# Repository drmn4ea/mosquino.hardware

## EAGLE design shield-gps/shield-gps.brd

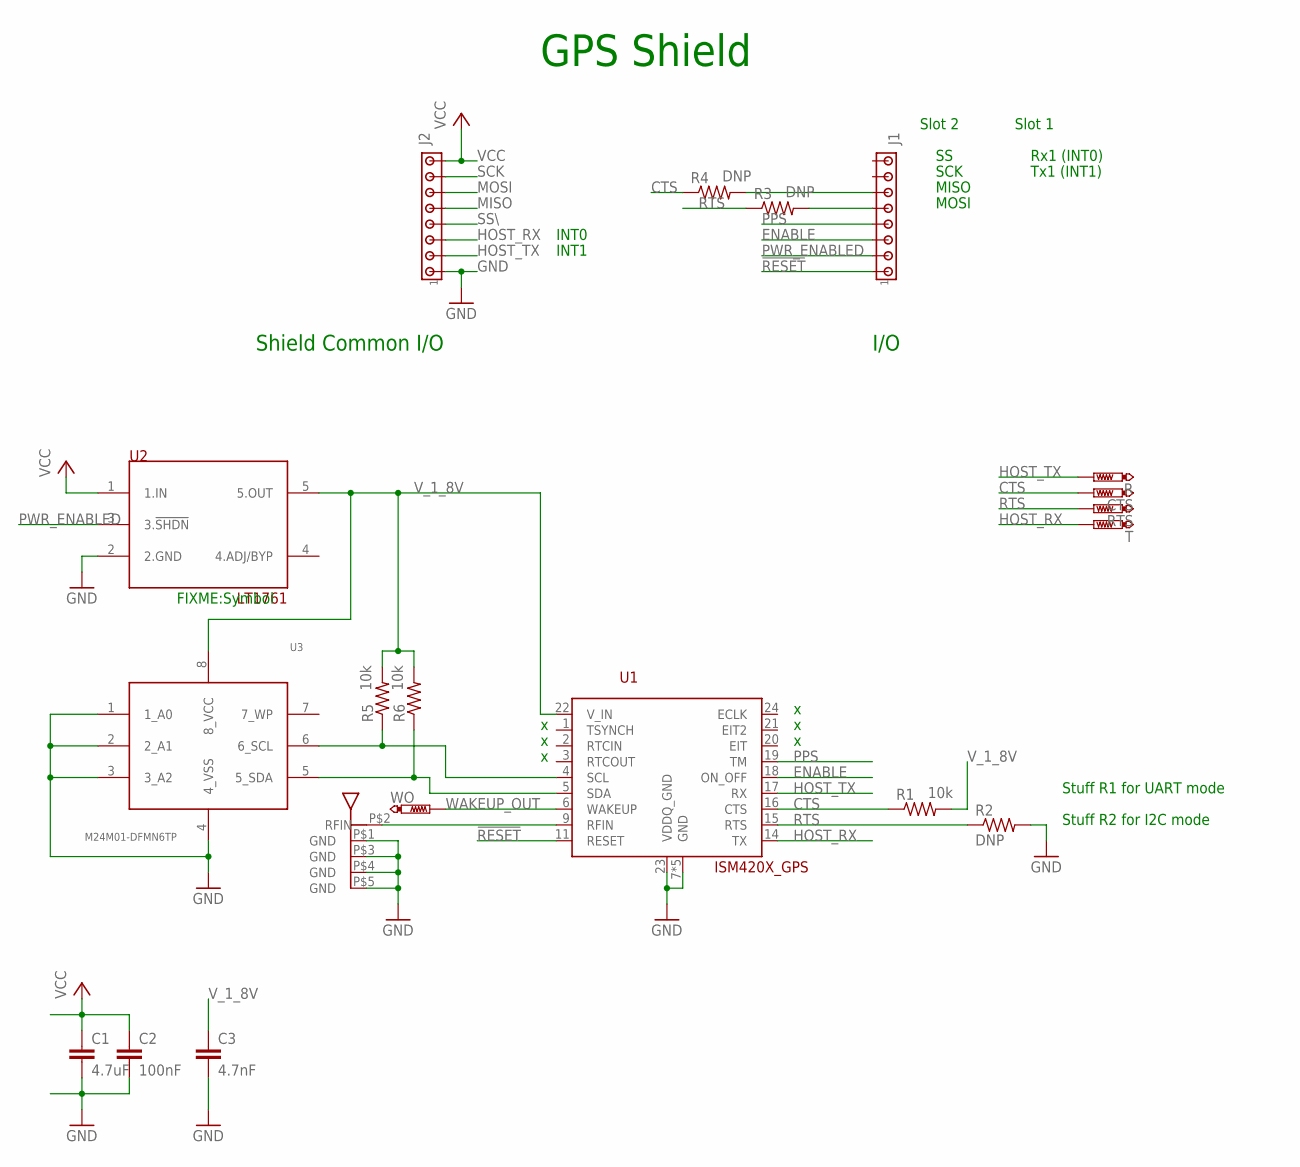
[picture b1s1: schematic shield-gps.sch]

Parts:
ANT1: A10204_ANTENNA
C1: 4.7uF; C0603
C2: 100nF; C0603
C3: 4.7nF; C0603
CTS: PTR1PAD1-13; P1-13
J1, J2: MTA08-100; 10X08MTA
R: PTR1PAD1-13; P1-13
R1, R5, R6: 10k; R0603
R2, R3, R4: DNP; R0603
RTS: PTR1PAD1-13; P1-13
T: PTR1PAD1-13; P1-13
U1: ISM420X_GPS
U2: TC1016-1.85VCTTR; SOT23-5
U3: M24M01-DFMN6TP; SO-8
WO: PTR1PAD1-13; P1-13

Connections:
!RESET: J1.1, U1.11 (RESET)
CTS: CTS.TP, R1.1, R4.1, U1.16 (CTS)
ENABLE: J1.3, U1.18 (ON_OFF)
GND: ANT1.P$1 (GND), ANT1.P$3 (GND), ANT1.P$4 (GND), ANT1.P$5 (GND), C1.2, C2.2, C3.2, J2.1, R2.2, U1.7 (GND), U1.8 (GND), U1.10 (GND), U1.12 (GND), U1.13 (GND), U1.23 (VDDQ_GND), U2.2 (2.GND), U3.1 (1_A0), U3.2 (2_A1), U3.3 (3_A2), U3.4 (4_VSS)
HOST_RX: J2.3, T.TP, U1.14 (TX)
HOST_TX: J2.2, R.TP, U1.17 (RX)
MISO: J2.5
MOSI: J2.6
unnamed: ANT1.P$2 (RFIN), U1.9 (RFIN)
unnamed: J1.5, R3.2
unnamed: R6.1, U1.5 (SDA), U3.5 (5_SDA)
unnamed: R5.1, U1.4 (SCL), U3.6 (6_SCL)
unnamed: J1.6, R4.2
PPS: J1.4, U1.19 (TM)
PWR_ENABLED: J1.2, U2.3 (3.!SHDN)
RTS: R2.1, R3.1, RTS.TP, U1.15 (RTS)
SCK: J2.7
SS\: J2.4
VCC: C1.1, C2.1, J2.8, U2.1 (1.IN)
V_1_8V: C3.1, R1.2, R5.2, R6.2, U1.22 (V_IN), U2.5 (5.OUT), U3.8 (8_VCC)
WAKEUP_OUT: U1.6 (WAKEUP), WO.TP

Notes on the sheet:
Shield Common I/O
I/O
GPS Shield
SCK
MISO
MOSI
Rx1 (INT0)
Tx1 (INT1)
Slot 2
Slot 1
INT1
INT0
FIXME:Symbol
Stuff R1 for UART mode
Stuff R2 for I2C mode

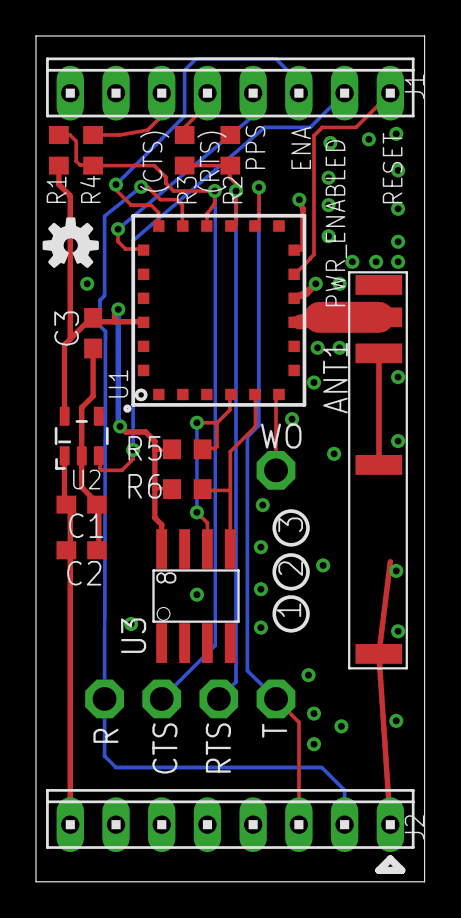
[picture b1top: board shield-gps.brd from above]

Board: 2 copper layers, 21.6 x 47.0 mm, 21 parts (0 on the bottom side), 17 nets.

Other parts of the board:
LOGO1: OSHW-LOGOS; OSHW-LOGO-S

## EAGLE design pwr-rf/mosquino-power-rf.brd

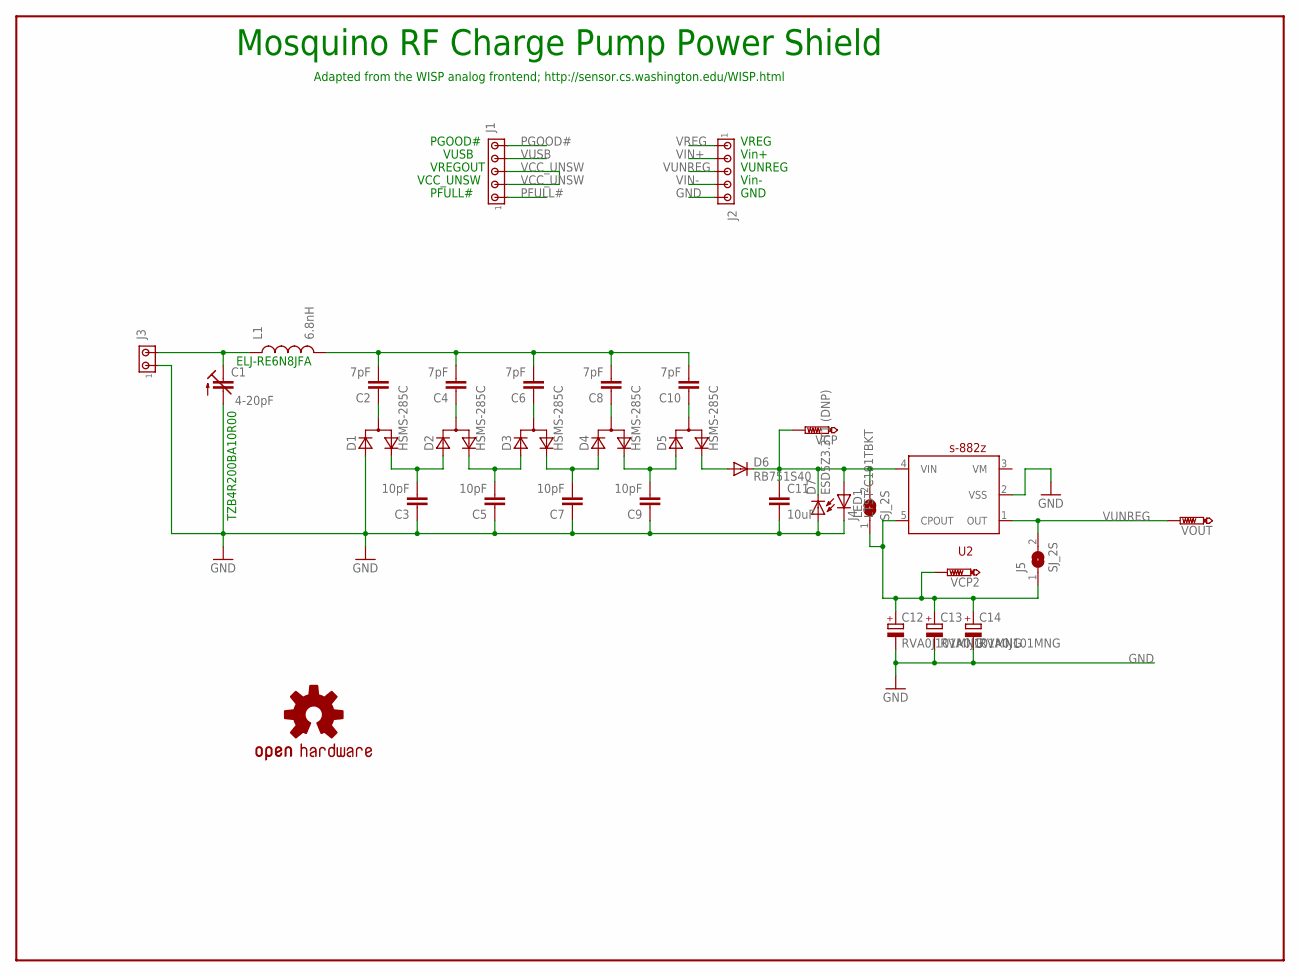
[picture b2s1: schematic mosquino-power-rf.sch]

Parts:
C1: 4-20pF; CTRIM3018_12
C2, C4, C6, C8, C10: 7pF; C0603
C3, C5, C7, C9: 10pF; C0603
C11: 10uF; C0805
C12, C13, C14: RVA0J101MNG; CASE_D
D1, D2, D3, D4, D5: HSMS-285C; SOT-323
D6: RB751S40; SOD523
D7: ESD5Z3.3T1 (DNP); SOD523
J1, J2: MTA05-100; 10X05MTA
J3: MTA02-100; 10X02MTA
J4, J5: SJ_2S; SJ2_S
L1: 6.8nH; 0603
LED1: LTST-C191TBKT; CHIP-LED0603
LOGO1: OSHW-LOGOS; OSHW-LOGO-S
U2: s-882z; SOT23-5
VCP, VCP2: PTR1PAD1-13; P1-13
VOUT: PTR1PAD1-13; P1-13

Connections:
GND: C1.- (A), C3.1, C5.1, C7.1, C9.1, C11.2, C12.2 (-), C13.2 (-), C14.2 (-), D1.1 (A), D7.A, J2.5, J3.1, LED1.C, U2.2 (VSS)
unnamed: C2.1, D1.3 (CA)
unnamed: C3.2, D1.2 (C), D2.1 (A)
unnamed: C5.2, D2.2 (C), D3.1 (A)
unnamed: C7.2, D3.2 (C), D4.1 (A)
unnamed: C9.2, D4.2 (C), D5.1 (A)
unnamed: C2.2, C4.2, C6.2, C8.2, C10.2, L1.2
unnamed: C4.1, D2.3 (CA)
unnamed: C6.1, D3.3 (CA)
unnamed: C8.1, D4.3 (CA)
unnamed: C10.1, D5.3 (CA)
unnamed: D5.2 (C), D6.A
unnamed: C1.+ (E), J3.2, L1.1
unnamed: C11.1, D6.C, D7.C, J4.2, LED1.A, U2.4 (VIN), VCP.TP
unnamed: C12.1 (+), C13.1 (+), C14.1 (+), J4.1, J5.1, U2.5 (CPOUT), VCP2.TP
PFULL#: J1.1
PGOOD#: J1.5
VCC_UNSW: J1.2, J1.3
VIN+: J2.2
VIN-: J2.4
VREG: J2.1
VUNREG: J2.3, J5.2, U2.1 (OUT), VOUT.TP
VUSB: J1.4

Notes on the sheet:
PGOOD#
Vin+
Vin-
GND
PFULL#
VUSB
VREG
VUNREG
VREGOUT
Mosquino RF Charge Pump Power Shield
VCC_UNSW
Adapted from the WISP analog frontend; http://sensor.cs.washington.edu/WISP.html
ELJ-RE6N8JFA
TZB4R200BA10R00

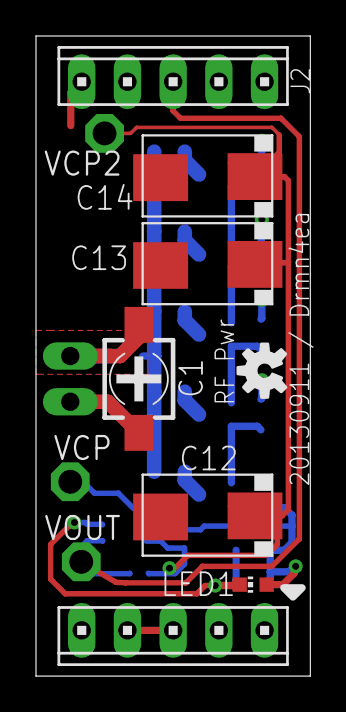
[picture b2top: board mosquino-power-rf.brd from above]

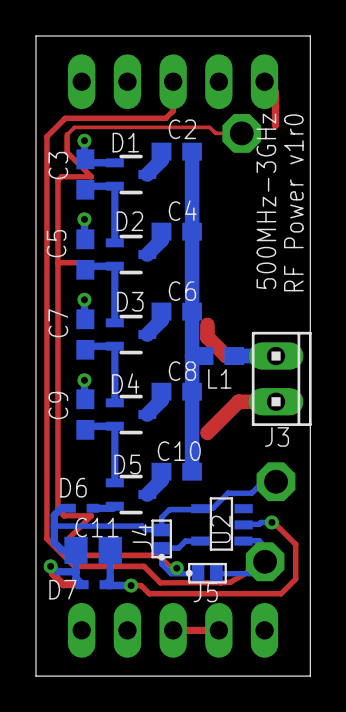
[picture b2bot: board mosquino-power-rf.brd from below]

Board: 2 copper layers, 15.2 x 35.6 mm, 33 parts (22 on the bottom side), 17 nets.

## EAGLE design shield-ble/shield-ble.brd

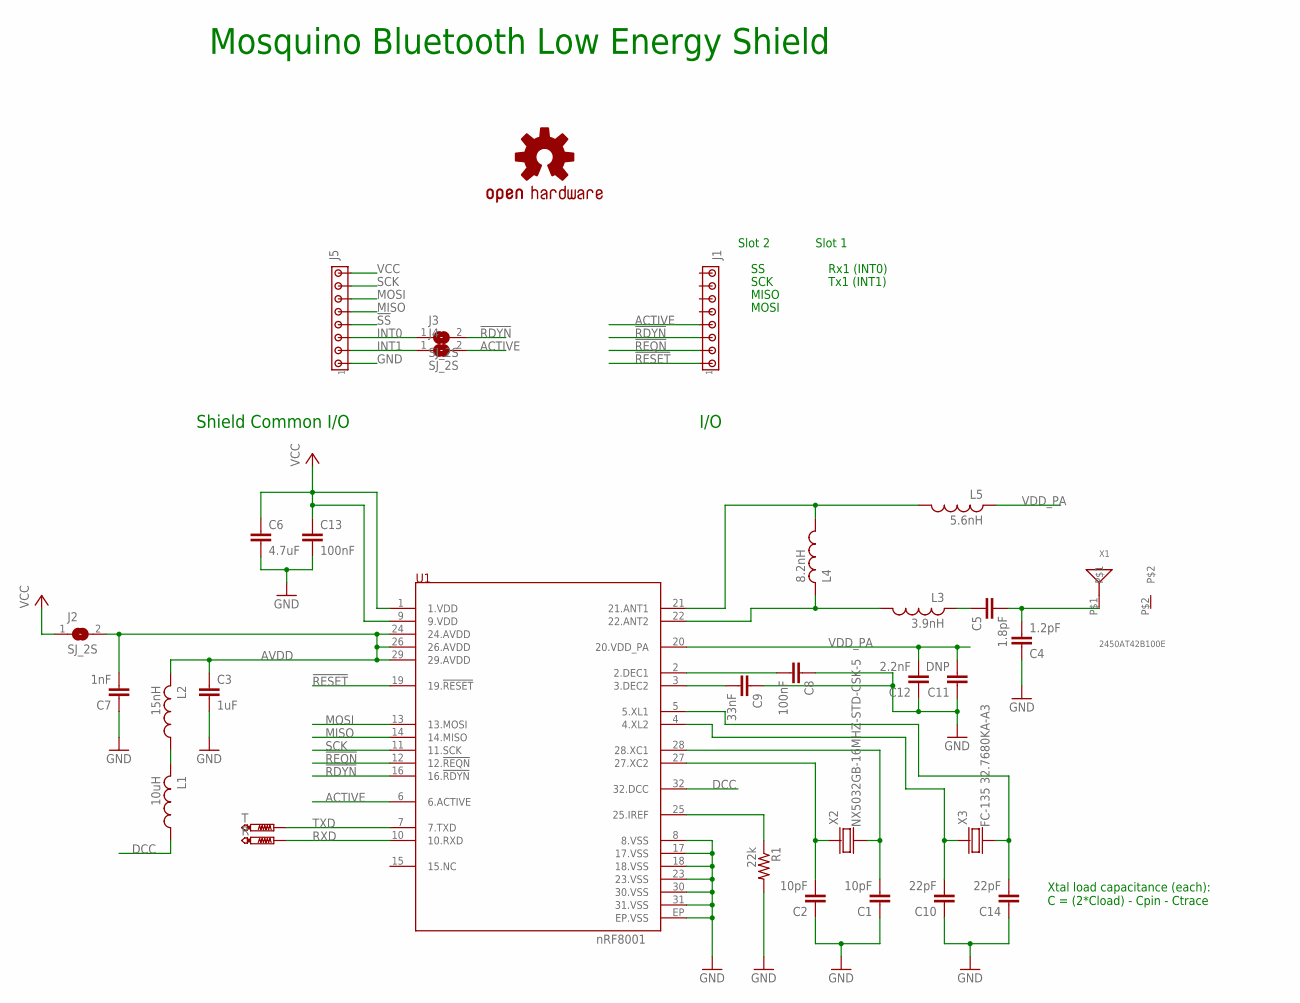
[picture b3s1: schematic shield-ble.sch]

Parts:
C1, C2: 10pF; C0603
C3: 1uF; C0603
C4: 1.2pF; C0603
C5: 1.8pF; C0603
C6: 4.7uF; C0603
C7: 1nF; C0603
C8, C13: 100nF; C0603
C9: 33nF; C0603
C10, C14: 22pF; C0603
C11: DNP; C0603
C12: 2.2nF; C0603
J1, J5: MTA08-100; 10X08MTA
J2, J3, J4: SJ_2S; SJ2_S
L1: 10uH; 0603
L2: 15nH; 0603
L3: 3.9nH; 0603
L4: 8.2nH; 0603
L5: 5.6nH; 0603
LOGO1: OSHW-LOGOS; OSHW-LOGO-S
R: PTR1PAD1-13; P1-13
R1: 22k; R0603
T: PTR1PAD1-13; P1-13
U1: NRF8001_QFN32; QFN-32
X1: 2450AT42B100E; ANTENNA_CHIP_5MMX2MM
X2: NX5032GB-16MHZ-STD-CSK-5; CRYSTAL_SMD_5X3POINT2MM
X3: FC-135 32.7680KA-A3; FC-135

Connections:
!RDYN: J1.3, J3.2, U1.16 (16.!RDYN)
!REQN: J1.2, U1.12 (12.!REQN)
!RESET: J1.1, U1.19 (19.!RESET)
!SS: J5.4
ACTIVE: J1.4, J4.2, U1.6 (6.ACTIVE)
AVDD: C3.1, C7.2, J2.2, L2.2, U1.24 (24.AVDD), U1.26 (26.AVDD), U1.29 (29.AVDD)
DCC: L1.1, U1.32 (32.DCC)
GND: C1.1, C2.1, C3.2, C4.1, C6.2, C7.1, C8.1, C9.1, C10.1, C11.1, C12.1, C13.2, C14.1, J5.1, R1.2, U1.8 (8.VSS), U1.17 (17.VSS), U1.18 (18.VSS), U1.23 (23.VSS), U1.30 (30.VSS), U1.31 (31.VSS), U1.EP (EP.VSS)
INT0: J3.1, J5.3
INT1: J4.1, J5.2
MISO: J5.5, U1.14 (14.MISO)
MOSI: J5.6, U1.13 (13.MOSI)
unnamed: L1.2, L2.1
unnamed: C2.2, U1.27 (27.XC2), X2.P$1 (X1)
unnamed: C1.2, U1.28 (28.XC1), X2.P$2 (X2)
unnamed: C10.2, U1.4 (4.XL2), X3.P$1 (X1)
unnamed: C14.2, U1.5 (5.XL1), X3.P$2 (X2)
unnamed: C5.1, L3.2
unnamed: L3.1, L4.2, U1.22 (22.ANT2)
unnamed: L4.1, L5.1, U1.21 (21.ANT1)
unnamed: C8.2, U1.2 (2.DEC1)
unnamed: C9.2, U1.3 (3.DEC2)
unnamed: R1.1, U1.25 (25.IREF)
unnamed: C4.2, C5.2, X1.P$1
RXD: R.TP, U1.10 (10.RXD)
SCK: J5.7, U1.11 (11.SCK)
TXD: T.TP, U1.7 (7.TXD)
VCC: C6.1, C13.1, J2.1, J5.8, U1.1 (1.VDD), U1.9 (9.VDD)
VDD_PA: C11.2, C12.2, L5.2, U1.20 (20.VDD_PA)

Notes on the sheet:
Shield Common I/O
I/O
Mosquino Bluetooth Low Energy Shield
SCK
MISO
MOSI
Rx1 (INT0)
Tx1 (INT1)
Slot 2
Slot 1
Xtal load capacitance (each): C = (2*Cload) - Cpin - Ctrace

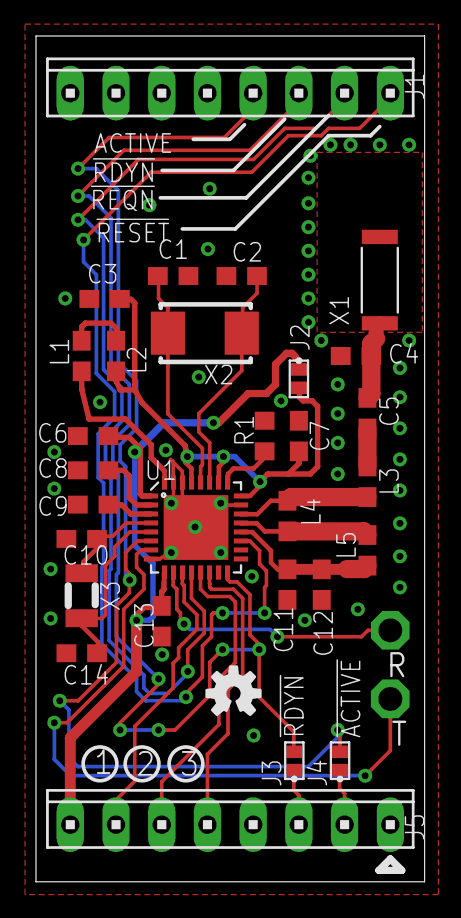
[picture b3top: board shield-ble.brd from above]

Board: 2 copper layers, 21.6 x 47.0 mm, 32 parts (0 on the bottom side), 28 nets.

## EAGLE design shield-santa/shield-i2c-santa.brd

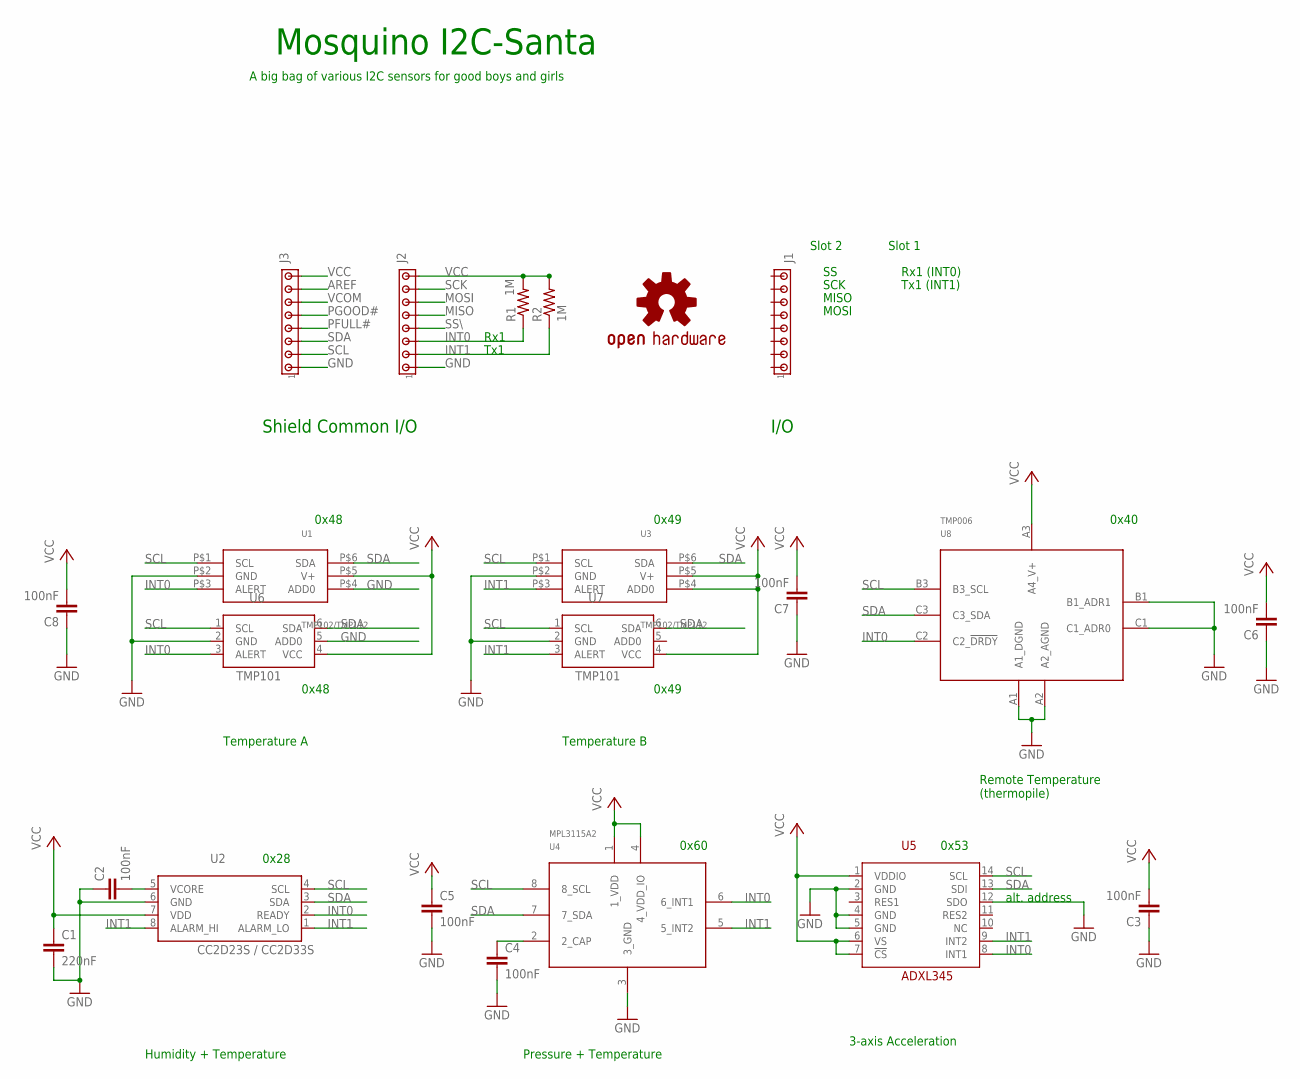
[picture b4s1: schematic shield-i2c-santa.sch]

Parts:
C1: 220nF; C0603
C2, C3, C4, C5, C6, C7, C8: 100nF; C0603
J1, J2, J3: MTA08-100; 10X08MTA
LOGO1: OSHW-LOGOS; OSHW-LOGO-S
R1, R2: 1M; R0603
U1, U3: TMP102/TMP112; SOT563
U2: CC2D23S / CC2D33S; CC2DXXX
U4: MPL3115A2; 8-LGA
U5: ADXL345; 14-LGA
U6, U7: TMP101; SOT23-6
U8: TMP006; 8-DSBGA

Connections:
AREF: J3.7
GND: C1.2, C2.1, C3.1, C4.2, C5.2, C6.1, C7.1, C8.1, J2.1, J3.1, U1.P$2 (GND), U1.P$4 (ADD0), U2.6 (GND), U3.P$2 (GND), U4.3 (3_GND), U5.2 (GND), U5.4 (GND), U5.5 (GND), U5.12 (SDO), U6.2 (GND), U6.5 (ADD0), U7.2 (GND), U8.A1 (A1_DGND), U8.A2 (A2_AGND), U8.B1 (B1_ADR1), U8.C1 (C1_ADR0)
INT0: J2.3, R1.1, U1.P$3 (ALERT), U2.2 (READY), U4.6 (6_INT1), U5.8 (INT1), U6.3 (ALERT), U8.C2 (C2_!DRDY)
INT1: J2.2, R2.1, U2.1 (ALARM_LO), U2.8 (ALARM_HI), U3.P$3 (ALERT), U4.5 (5_INT2), U5.9 (INT2), U7.3 (ALERT)
MISO: J2.5
MOSI: J2.6
unnamed: C2.2, U2.5 (VCORE)
unnamed: C4.1, U4.2 (2_CAP)
PFULL#: J3.4
PGOOD#: J3.5
SCK: J2.7
SCL: J3.2, U1.P$1 (SCL), U2.4 (SCL), U3.P$1 (SCL), U4.8 (8_SCL), U5.14 (SCL), U6.1 (SCL), U7.1 (SCL), U8.B3 (B3_SCL)
SDA: J3.3, U1.P$6 (SDA), U2.3 (SDA), U3.P$6 (SDA), U4.7 (7_SDA), U5.13 (SDI), U6.6 (SDA), U7.6 (SDA), U8.C3 (C3_SDA)
SS\: J2.4
VCC: C1.1, C3.2, C5.1, C6.2, C7.2, C8.2, J2.8, J3.8, R1.2, R2.2, U1.P$5 (V+), U2.7 (VDD), U3.P$4 (ADD0), U3.P$5 (V+), U4.1 (1_VDD), U4.4 (4_VDD_IO), U5.1 (VDDIO), U5.6 (VS), U5.7 (!CS), U6.4 (VCC), U7.4 (VCC), U8.A3 (A4_V+)
VCOM: J3.6

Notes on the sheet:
Shield Common I/O
I/O
Mosquino I2C-Santa
A big bag of various I2C sensors for good boys and girls
SCK
MISO
MOSI
Rx1 (INT0)
Tx1 (INT1)
Slot 2
Slot 1
Tx1
Rx1
0x53
alt. address
0x48
0x49
0x40
0x28
0x60
Pressure + Temperature
3-axis Acceleration
Humidity + Temperature
Remote Temperature (thermopile)
Temperature A
Temperature B

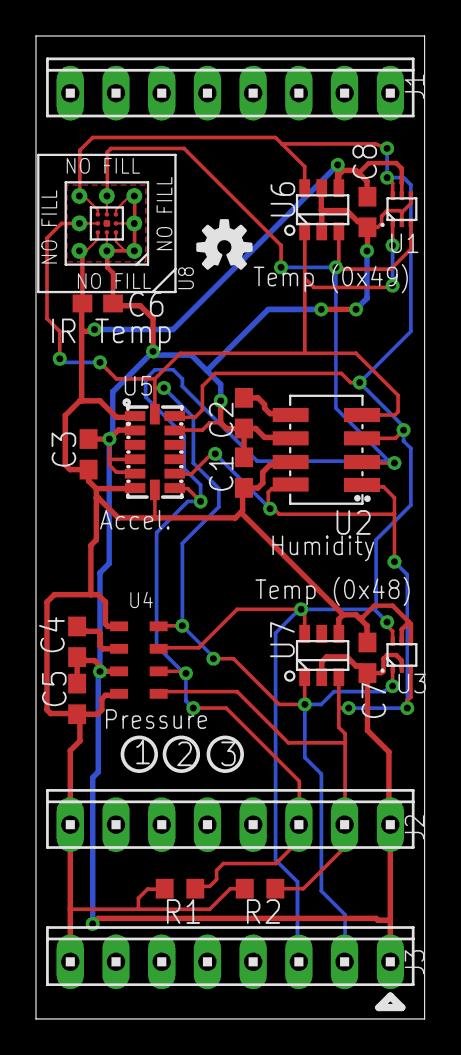
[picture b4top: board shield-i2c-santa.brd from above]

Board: 2 copper layers, 21.6 x 54.6 mm, 22 parts (0 on the bottom side), 8 nets.

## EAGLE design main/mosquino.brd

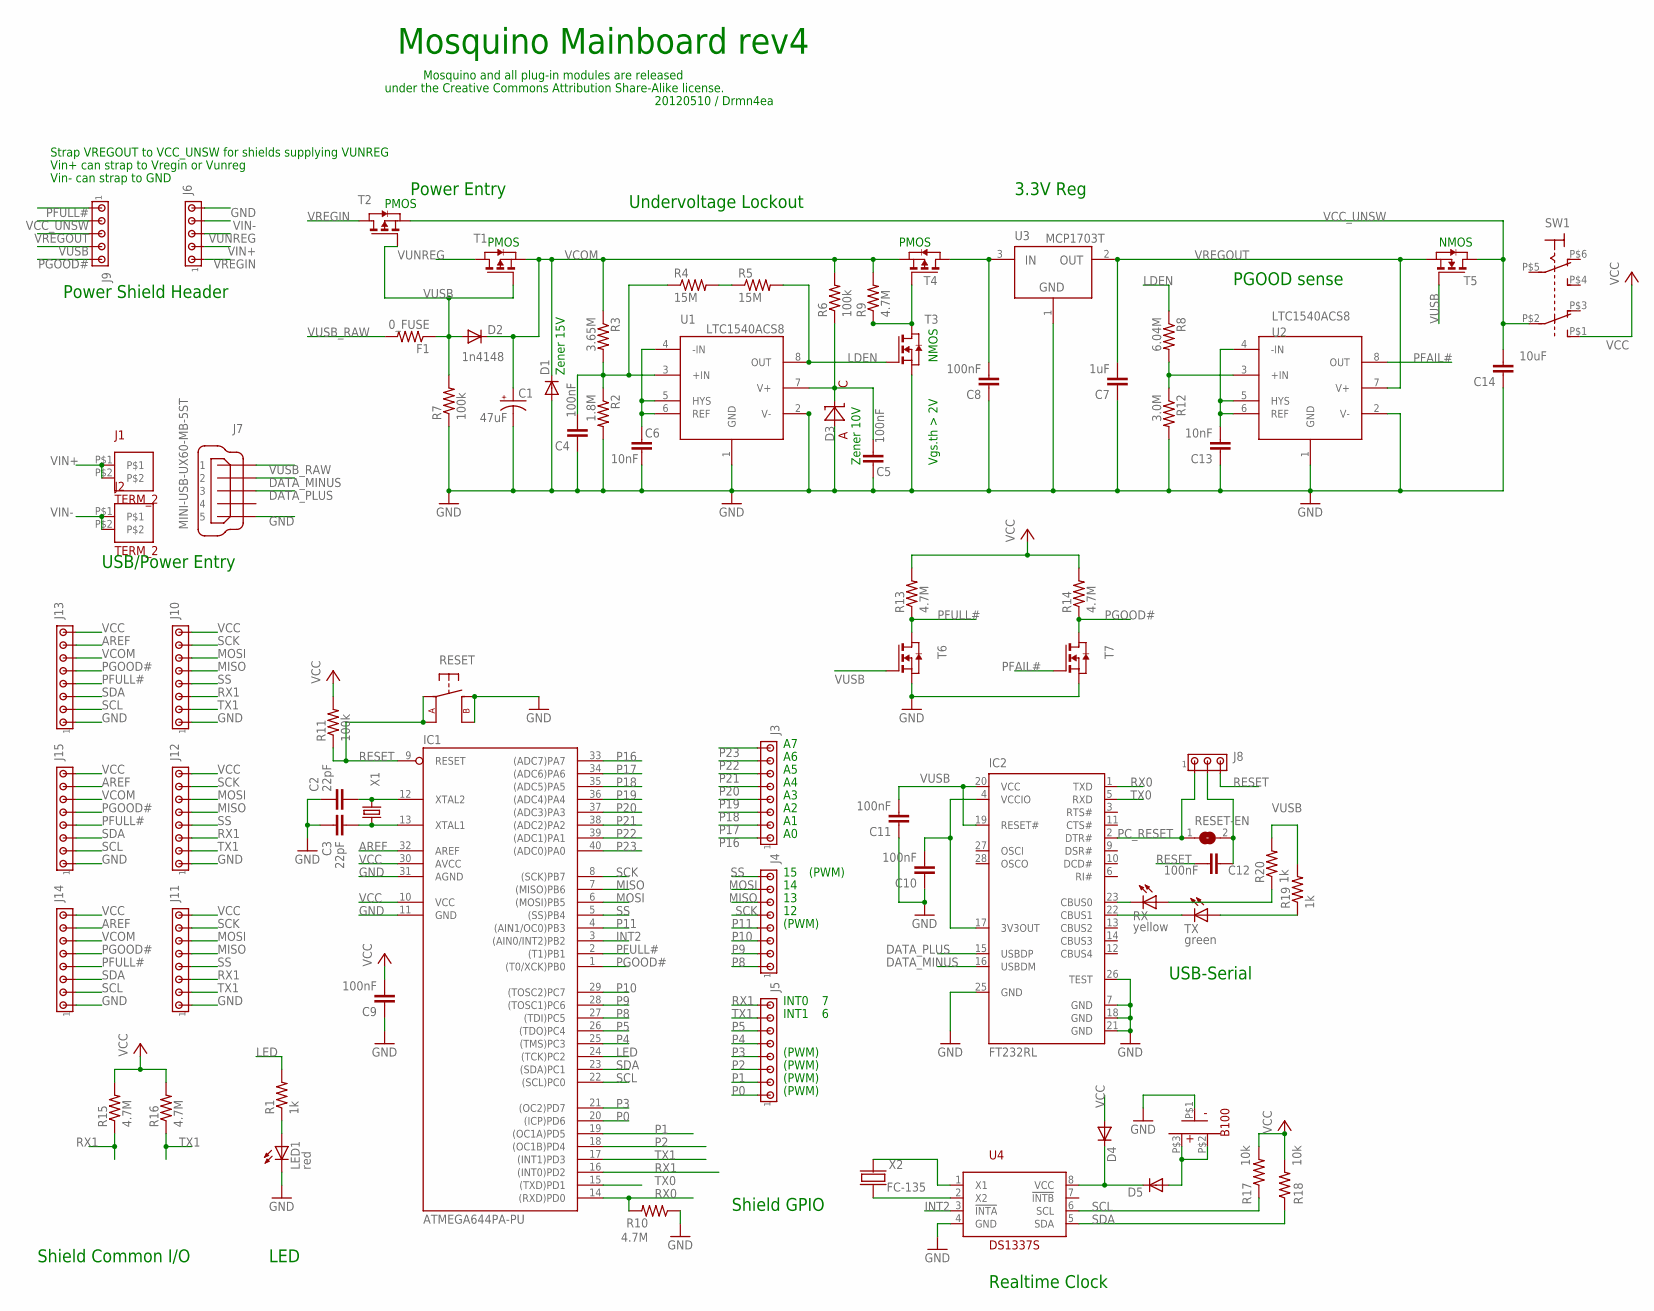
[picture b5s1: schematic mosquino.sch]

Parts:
B100: BK885_CR1225_COIN_BATTERY_HOLDER_SMD
C1: 47uF; PANASONIC_D
C2, C3: 22pF; C0805K
C4, C5, C8: 100nF; C0805
C6, C13: 10nF; C0805
C7: 1uF; C0805
C9, C10, C11, C12: 100nF; C0805K
C14: 10uF; C0805K
D1: BZT52C15-7-F; SOD123
D2: 1n4148; SOD123
D3: BZT52C10-7-F; SOD123
D4, D5: MMSD301T1G; SOD123
F1: 0_FUSE; R0805
IC1: ATMEGA644PA-PU; DIL40
IC2: FT232RL; SSOP28
J1, J2: TERM_2; TERM_3POINT5MM
J3, J4, J5, J10, J11, J12, J13, J14, J15: MTA08-100; 10X08MTA
J6, J9: MTA05-100; 10X05MTA
J7: MINI-USB-UX60-MB-5ST; UX60-MB-5ST
J8: MTA03-100; 10X03MTA
LED1: red; CHIP-LED0805
R1, R19, R20: 1k; R0805
R2: 1.8M; R0805
R3: 3.65M; R0805
R4, R5: 15M; R0805
R6, R7, R11: 100k; R0805
R8: 6.04M; R0805
R9, R10, R13, R14, R15, R16: 4.7M; R0805
R12: 3.0M; R0805
R17, R18: 10k; R0805
RESET: EVQ_TACT_SW_6X6POINT5
RESET-EN: SJ
RX: yellow; CHIP-LED0805
SW1: SW_DPDT_EG1390; EG1390_SWITCH_DPDT
T1, T2, T4: DMP3098L-7; SOT-23
T3, T6, T7: IRFML8244TRPBF; SOT-23
T5: BSH103; SOT-23
TX: green; CHIP-LED0805
U1, U2: LTC1540ACS8; SO-8
U3: MCP1703T; SOT23
U4: DS1337S; SO-8
X1: ABLS-4.000MHZ-B4-T; SM49
X2: FC-135

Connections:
AREF: IC1.32 (AREF), J13.7, J14.7, J15.7
DATA_MINUS: IC2.16 (USBDM), J7.2
DATA_PLUS: IC2.15 (USBDP), J7.3
GND: B100.P$1 (-), C1.-, C2.2, C3.1, C4.1, C5.1, C6.1, C7.1, C8.1, C9.1, C10.1, C11.1, C13.1, C14.1, D1.A, D3.A, IC1.11 (GND), IC1.31 (AGND), IC2.7 (GND), IC2.18 (GND), IC2.21 (GND), IC2.25 (GND), IC2.26 (TEST), J6.5, J7.5, J10.1, J11.1, J12.1, J13.1, J14.1, J15.1, LED1.C, R2.2, R7.1, R10.1, R12.2, RESET.B, RESET.B2 (B1), T3.2 (S), T6.2 (S), T7.2 (S), U1.1 (GND), U1.2 (V-), U2.1 (GND), U2.2 (V-), U3.1 (GND), U4.4 (GND)
INT2: IC1.3 ((AIN0/INT2)PB2), U4.3 (!INTA)
LDEN: R5.2, R8.1, T3.3 (G), U1.8 (OUT)
LED: IC1.24 ((TCK)PC2), R1.2
MISO: IC1.7 ((MISO)PB6), J4.6, J10.5, J11.5, J12.5
MOSI: IC1.6 ((MOSI)PB5), J4.7, J10.6, J11.6, J12.6
unnamed: C12.1, J8.2, RESET-EN.2
unnamed: C2.1, IC1.12 (XTAL2), X1.2
unnamed: LED1.A, R1.1
unnamed: IC2.22 (CBUS1), TX.C
unnamed: C3.2, IC1.13 (XTAL1), X1.1
unnamed: U4.2 (X2), X2.P$2 (X2)
unnamed: D4.C, D5.C, U4.8 (VCC)
unnamed: U4.1 (X1), X2.P$1 (X1)
unnamed: C10.2, IC2.4 (VCCIO), IC2.17 (3V3OUT)
unnamed: R20.1, RX.A
unnamed: C5.2, D3.C, R6.1, U1.7 (V+)
unnamed: C6.2, U1.4 (-IN), U1.5 (HYS), U1.6 (REF)
unnamed: IC2.23 (CBUS0), RX.C
unnamed: R19.1, TX.A
unnamed: B100.P$2 (+), B100.P$3 (+), D5.A
unnamed: C4.2, R2.1, R3.2, R4.1, U1.3 (+IN)
unnamed: C13.2, U2.4 (-IN), U2.5 (HYS), U2.6 (REF)
unnamed: R8.2, R12.1, U2.3 (+IN)
unnamed: C8.2, T4.1 (D), U3.3 (IN)
unnamed: R9.1, T3.1 (D), T4.3 (G)
unnamed: R4.2, R5.1
P0: IC1.20 ((ICP)PD6), J5.1
P1: IC1.19 ((OC1A)PD5), J5.2
P2: IC1.18 ((OC1B)PD4), J5.3
P3: IC1.21 ((OC2)PD7), J5.4
P4: IC1.25 ((TMS)PC3), J5.5
P5: IC1.26 ((TDO)PC4), J5.6
P8: IC1.27 ((TDI)PC5), J4.1
P9: IC1.28 ((TOSC1)PC6), J4.2
P10: IC1.29 ((TOSC2)PC7), J4.3
P11: IC1.4 ((AIN1/OC0)PB3), J4.4
P16: IC1.33 ((ADC7)PA7), J3.1
P17: IC1.34 ((ADC6)PA6), J3.2
P18: IC1.35 ((ADC5)PA5), J3.3
P19: IC1.36 ((ADC4)PA4), J3.4
P20: IC1.37 ((ADC3)PA3), J3.5
P21: IC1.38 ((ADC2)PA2), J3.6
P22: IC1.39 ((ADC1)PA1), J3.7
P23: IC1.40 ((ADC0)PA0), J3.8
PC_RESET: IC2.2 (DTR#), J8.1, RESET-EN.1
PFAIL#: T7.3 (G), U2.8 (OUT)
PFULL#: IC1.2 ((T1)PB1), J9.1, J13.4, J14.4, J15.4, R13.1, T6.1 (D)
PGOOD#: IC1.1 ((T0/XCK)PB0), J9.5, J13.5, J14.5, J15.5, R14.1, T7.1 (D)
RESET: C12.2, IC1.9 (RESET), J8.3, R11.1, RESET.A, RESET.A2 (A1)
RX0: IC1.14 ((RXD)PD0), IC2.1 (TXD), R10.2
RX1: IC1.16 ((INT0)PD2), J5.8, J10.3, J11.3, J12.3, R15.1
SCK: IC1.8 ((SCK)PB7), J4.5, J10.7, J11.7, J12.7
SCL: IC1.22 ((SCL)PC0), J13.2, J14.2, J15.2, R17.1, U4.6 (SCL)
SDA: IC1.23 ((SDA)PC1), J13.3, J14.3, J15.3, R18.1, U4.5 (SDA)
SS: IC1.5 ((SS)PB4), J4.8, J10.4, J11.4, J12.4
TX0: IC1.15 ((TXD)PD1), IC2.5 (RXD)
TX1: IC1.17 ((INT1)PD3), J5.7, J10.2, J11.2, J12.2, R16.1
VCC: C9.2, D4.A, IC1.10 (VCC), IC1.30 (AVCC), J10.8, J11.8, J12.8, J13.8, J14.8, J15.8, R11.2, R13.2, R14.2, R15.2, R16.2, R17.2, R18.2, SW1.P$1 (ON1)
VCC_UNSW: C14.2, J9.2, SW1.P$2 (COM1), T2.2 (S), T5.1 (D)
VCOM: C1.+, D1.C, D2.C, J13.6, J14.6, J15.6, R3.1, R6.2, R9.2, T1.2 (S), T4.2 (S)
VIN+: J1.P$1, J1.P$2, J6.2
VIN-: J2.P$1, J2.P$2, J6.4
VREGIN: J6.1, T2.1 (D)
VREGOUT: C7.2, J9.3, T5.2 (S), U2.7 (V+), U3.2 (OUT)
VUNREG: J6.3, T1.1 (D)
VUSB: C11.2, D2.A, F1.1, IC2.19 (RESET#), IC2.20 (VCC), J9.4, R7.2, R19.2, R20.2, T1.3 (G), T2.3 (G), T5.3 (G), T6.3 (G)
VUSB_RAW: F1.2, J7.1

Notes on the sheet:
INT1
INT0
PMOS
Mosquino Mainboard rev4
20120510 / Drmn4ea
Strap VREGOUT to VCC_UNSW for shields supplying VUNREG
Vin+ can strap to Vregin or Vunreg
Vin- can strap to GND
Power Entry
USB-Serial
Realtime Clock
Shield GPIO
Shield Common I/O
LED
Power Shield Header
USB/Power Entry
Mosquino and all plug-in modules are released
under the Creative Commons Attribution Share-Alike license.
Undervoltage Lockout
NMOS
Vgs.th > 2V
3.3V Reg
PGOOD sense
Zener 15V
Zener 10V
(PWM)

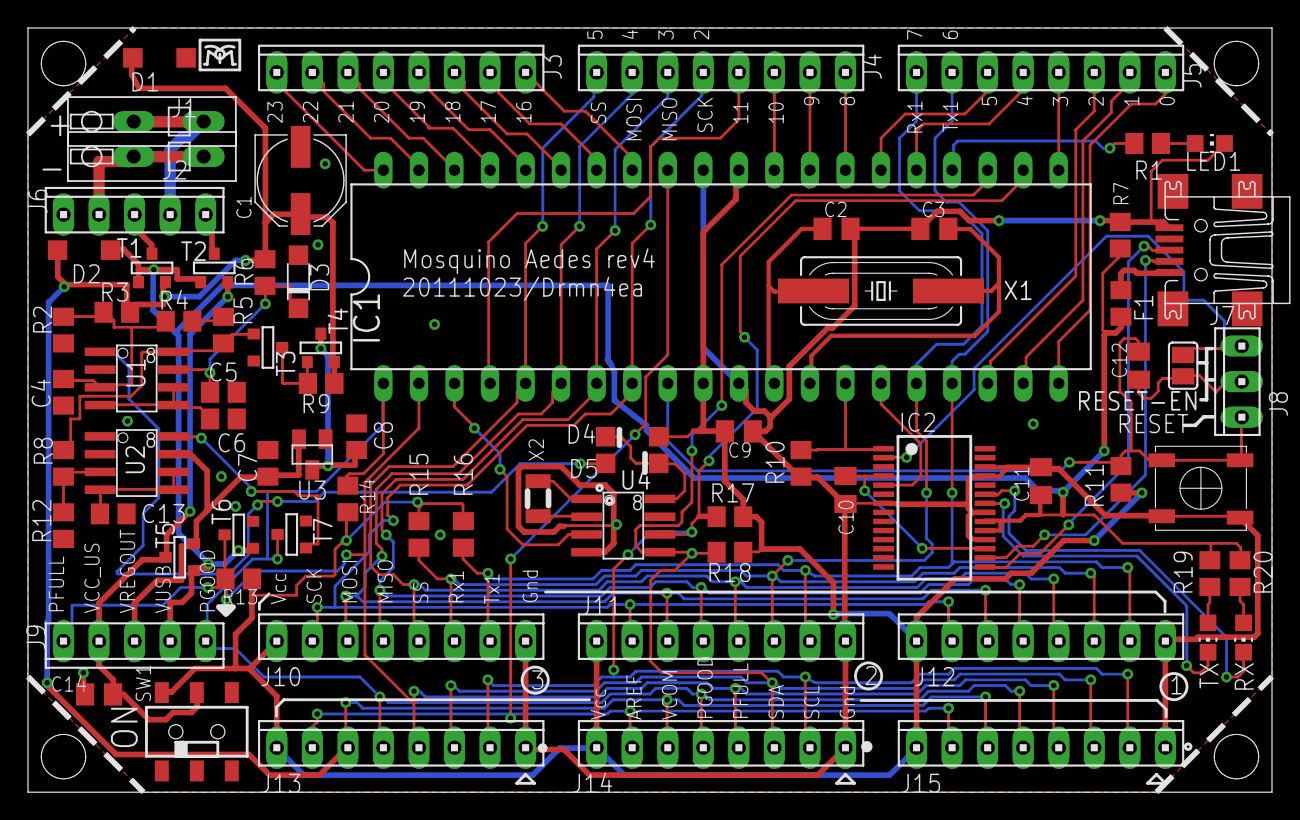
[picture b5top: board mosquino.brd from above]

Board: 2 copper layers, 88.9 x 54.6 mm, 77 parts (1 on the bottom side), 71 nets.

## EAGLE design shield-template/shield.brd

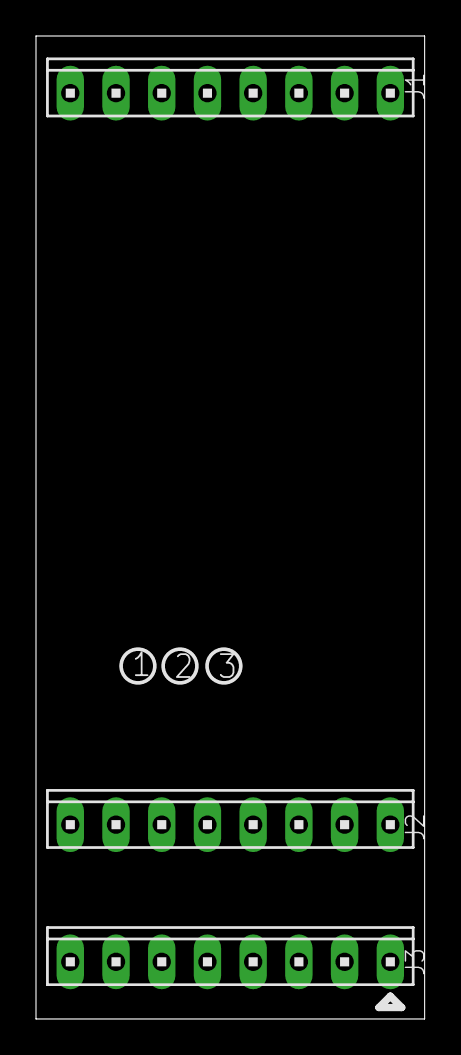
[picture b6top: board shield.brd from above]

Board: 2 copper layers, 21.6 x 54.6 mm, 3 parts (0 on the bottom side), 2 nets, no tracks yet.

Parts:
J1, J2, J3: 10X08MTA

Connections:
GND: J2.1, J3.1
VCC: J2.8, J3.8

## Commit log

2011-03-30 Add all current PCBs to hardware repository.
2011-06-02 Reorganized (and added / removed) power shield pinout to include more important signals. Added PFULL# signal (supplants BUS_SENSE signal); PGOOD# and PFULL# are active-low, wired-OR. Fixed voltage dr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
2011-06-02 First addition. Stackable power shield provides Li-Ion / LiPol / thinfilm battery support.
2011-06-02 Added open-drain PGOOD#; clarified inductor "pin 1" markings
2011-06-02 Added rectifier "boosted" mode jumper and FET for PGOOD#.
2011-06-02 First addition. 0.6V to (1.8 ~ 5V) booster for solar (e.g. "AA" walk light) and other low-voltage sources.
2011-06-02 First addition. Template and instructions for Mosquino power shields.
2011-06-02 Updated Kent Displays bistable display shield for Mosquino rev2 pinout. Moved ribbon footprint and electronics so that the display can be placed without folding the ribbon.
2011-06-02 Updated pinout for Mosquino rev2.
2011-06-02 Updated pinout for Mosquino rev2. Updated explanatory text slightly.
2011-06-02 Removed superfluous '+' symbols from mainboard. Flipped power shield PCBs in EAGLE for consistency with mainboard Added thermal vias to lipol board.
2011-06-02 Adding gerbers to the repository.
2011-06-08 Added dummy values for unknown (not yet calculated) resistors so they will have unique lines when the BOM is generated. Fixed / cleaned up a couple part numbers (regulator, supervisor) to match the e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
2011-06-08 Updated BOM to match rev2 final board.
2011-06-18 Added BOM for lipol and stepup boards. Update schematics and BOM for several boards to include complete part#s and vendor part#.
2011-07-20 Mainboard: Add proper resistor values to UVLO circuit, fix bottom solder mask, clean up silkscreen and bumped rev.
2011-07-20 Kent LCD shield: Changed all passive component footprints from 0603 to 0805. Added descriptive text for J1 jumper.
2012-01-25 Full power supply section redesign - now ~1uA in UVLO, ~6uA sleeping and supports voltages up to 15V; more reliable PGOOD and UVLO (on: 3.7V; off:3.3V) support. RESET pinned out near USB cable for ea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
2012-01-25 BOMs updated to share #s for common parts
2012-01-25 Designed out obsolete Sparkfun card socket; added multi-socket compatible footprint and new part #s.
2012-02-07 Decouple VREF. Fix poorly-working PGOOD signal.
2012-02-07 First addition. NOTE: Completely untested as of 2/7/2011; waiting on boards!
2012-02-07 First addition. I/O shield / Breakout board for ANT radio modules (AP2, AT3 recommended, although all currently sold have the same footprint).
2012-03-27 Update the part variant listed for IC1 in schematic to match BOM. (This part comes in several minor variants with their pinouts flipped various ways)
2012-06-12 No circuit changes for this commit. Mainboard: added schematic text indicating hardware PWM pins. Templates: Cleaned up explanatory text and/or silkscreen.
2013-10-14 Add i2c-santa shield v1r0 to repository.
2013-10-14 Added Bluetooth Low Energy shield v1r0 to repository.
2013-10-14 Added RF power shield v1r0 to repository.
2015-02-09 Add GPS shield to repository.

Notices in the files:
parts and their libraries:
SparkFun-Passives: Licensing: CC v3.0 Share-Alike You are welcome to use this library for commercial purposes.
